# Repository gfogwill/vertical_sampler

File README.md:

# Vertical Sampler

Firmware, hardware and host software for a balloon-borne vertical air sampler for Ice Nucleating Particle (INP) collection.

Payload and ground-station Raspberry Pi Pico W boards run **CircuitPython** and
communicate over **LoRa at 868 MHz**. The system supports the airborne payloads
`alma` and `beni`, plus the ground-operated payload `carla`.

## System Overview

```text
┌─────────────────────────┐        LoRa 868 MHz         ┌─────────────────────────┐
│        PAYLOAD          │◄───────────────────────────►│    GROUND STATION       │
│  Raspberry Pi Pico W    │                             │  Raspberry Pi Pico W    │
│                         │                             │                         │
│  - GPS (+ RTC sync)     │                             │  - Receives telemetry   │
│  - SHT85 RH/temp sensor │                             │  - Relays to PC via USB │
│  - LPS25H pressure      │                             │  - Forwards commands    │
│  - Pumps + optional     │                             └─────────────────────────┘
│    electrovalve / OPC   │
│  - SD logging           │                                         │
│  - Battery + flow meter │                                    USB Serial
│  - Watchdog             │                                         │
└─────────────────────────┘                             ┌─────────────────────────┐
                                                        │       Host computer     │
                                                        │ host/cli.py             │
                                                        │ host/quickview.py       │
                                                        └─────────────────────────┘
```

## Repository Structure

```text
vertical_sampler/
├── firmware/                    # CircuitPython code deployed to Pico boards
│   ├── common/                  # Copied flat to every CIRCUITPY drive
│   │   ├── config.py            # PCB v1 GPIOs, calibration, limits, LoRa addresses
│   │   ├── payload.py           # Active payload drivers and mission loop
│   │   ├── lora.py              # RFM9x wrapper
│   │   ├── pressure_sensor.py   # LPS25H driver
│   │   ├── sdcard.py            # SD mount, JSONL data and log writes
│   │   ├── logging.py
│   │   ├── pack.py              # Binary LoRa telemetry format
│   │   ├── led.py
│   │   ├── adafruit_gps.py      # Vendored CircuitPython dependency
│   │   └── adafruit_rfm9x.py    # Vendored CircuitPython dependency
│   ├── alma_main.py             # Alma airborne payload entry point
│   ├── beni_main.py             # Beni airborne payload entry point
│   ├── carla_main.py            # Carla ground payload entry point
│   └── ground_main.py           # Ground-station entry point
├── host/                        # Python 3 programs running on the control PC
│   ├── cli.py
│   └── quickview.py
├── pcb/                         # KiCad PCB v1 project
├── docs/
│   └── TROUBLESHOOTING.md
├── Makefile
└── README.md
```

`firmware/common/` is copied as flat modules to the root of `CIRCUITPY`. CircuitPython imports therefore remain simple:

```python
import config
import lora
import pack
```

## Payload Identities

| Unit | LoRa node address | Hardware | Entry point |
|---|---:|---|---|
| Ground station | `0x47` | Serial/LoRa bridge | `firmware/ground_main.py` |
| Alma | `0x93` | Two pumps, electro-valve, OPC-N3 | `firmware/alma_main.py` |
| Beni | `0x71` | Two pumps, electro-valve, OPC-N3 | `firmware/beni_main.py` |
| Carla | `0x72` | Front pump only; no electro-valve or OPC-N3 | `firmware/carla_main.py` |

Addresses, GPIO assignments, calibration constants and safety limits are defined centrally in `firmware/common/config.py`.

## Quick Start

### 1. Flash CircuitPython

```bash
make download-circuitpython-image
```

Copy the resulting `.uf2` to the Pico W while it is in BOOTSEL mode.

### 2. Install dependencies

The repository vendors `adafruit_gps.py` and `adafruit_rfm9x.py`. Install the remaining required CircuitPython libraries in the Pico `lib/` directory, including the dependencies required by the RFM9x driver such as `adafruit_bus_device`.

### 3. Deploy firmware

Set the CircuitPython mount point if needed:

```bash
export CIRCUITPY_PATH=/media/$USER/CIRCUITPY
```

Deploy the required device image:

```bash
make update-alma
make update-beni
make update-carla
make update-ground
```

Each target:

1. Removes stale `code.py`.
2. Copies all `firmware/common/*.py` modules to the Pico.
3. Copies the selected entry point as `main.py`.

### 4. Control a payload

Run commands from the host computer:

```bash
python host/cli.py data alma
python host/cli.py pump alma front on
python host/cli.py pump beni back off
python host/cli.py valve beni on
python host/cli.py data carla
python host/cli.py pump carla front on
```

For bench testing, the Alma or Beni payload can also accept actuator commands
directly over its own USB connection. Deploy the updated payload firmware first,
then run the USB helper from the laptop:

```bash
python host/usb_payload.py --port /dev/ttyACM0 pump front on
python host/usb_payload.py --port /dev/ttyACM0 data
python host/usb_payload.py --port /dev/ttyACM0 pump front off
```

The `--port` option can be omitted when exactly one Pico serial device is
connected. The helper waits for a JSON acknowledgement and exits; the pump
state is not tied to the helper process or USB connection. Alma/Beni must
remain separately powered after the laptop is disconnected, and the normal
battery/temperature safety interlock still applies. The direct USB path
accepts `pump front|back|both on|off`, `valve on|off`, and `data`.

Scheduled commands can be sent from a text file using UTC ISO-8601
timestamps. The command after each timestamp uses the same syntax as the
one-shot CLI commands:

```text
# timestamp command payload [location] state
2026-09-26T12:00:00Z pump alma front on
2026-09-26T12:30:00Z valve beni off
2026-09-26T13:00:00+00:00 pump alma front off
```

An editable example is provided in
[`sampling_schedule.example.txt`](sampling_schedule.example.txt). Copy it
to a working schedule, then change and review the timestamps before running:

```bash
cp sampling_schedule.example.txt sampling_schedule.txt
python host/cli.py schedule sampling_schedule.txt --dry-run
```

Run the schedule with:

```bash
python host/cli.py schedule sampling_schedule.txt
```

To run the schedule together with the monitor and JSON telemetry logging,
use the monitor mode so both features share one serial connection:

```bash
python host/cli.py monitor \
  --schedule sampling_schedule.txt \
  --json-output telemetry.jsonl
```

`--json-output` is an alias for `--log-file`. Add
`--schedule-run-past-due` if entries from before startup should be executed
immediately.

Entries that are already past when the scheduler starts are skipped by
default. Use `--run-past-due` to execute them immediately, or
`--dry-run` to validate and print the schedule without sending commands.
For scheduled actuator commands, the host by default waits 5 seconds after
each send, requests fresh payload telemetry, and checks the requested pump or
valve state. If the state is not confirmed, the command is sent again, up to
three total attempts. A command that was applied but whose acknowledgement was
lost is not resent when the later state check confirms the requested state.

The standalone scheduler accepts `--verify-delay SECONDS` and
`--max-attempts COUNT`. Monitor schedules use the corresponding
`--schedule-verify-delay` and `--schedule-max-attempts` options. These options
apply only to pump and valve commands; `data` entries retain their existing
telemetry retry behavior.

`host/quickview.py` is available for local data inspection and visualization.
It displays separate Alma and Beni OPC-N3 heatmaps using the standard
0.35–40 µm diameter bins on a logarithmic diameter axis. Heatmap colors use
logarithmic normalization and are corrected to counts per logarithmic diameter
interval (`dN/dlog10(Dp)`). New telemetry includes the OPC histogram sample
period, so QuickView and the plotting scripts normalize distributions to
particles/cm³. Older logs without that field remain relative unless a known
period is passed explicitly, for example:

```bash
python host/quickview.py --log-file ground_dump.jsonl \
    --opc-sampling-period-s <seconds>
```
All shared time axes are explicitly formatted in UTC. QuickView prefers the
payload UTC/RTC timestamp, then the host log timestamp; when a payload has no
valid absolute clock, its `monotonic_s` intervals are retained instead of
assigning one artificial second per log line.
Carla is included in the common sensor plots but has no OPC or electro-valve
controls.

For daily low-cloud measurement planning at Matorova, install the weather
dashboard dependencies and launch:

```bash
python -m pip install -r host/requirements-weather.txt
python host/weather_dashboard.py
```

The dashboard refreshes every 10 minutes and combines:

- ECMWF IFS boundary-layer height, retrieved through Open-Meteo.
- Altitude-resolved cloud fraction from Cloudnet's preferred forecast model
  for Kenttärova (normally MEPS), with liquid, ice and precipitating
  hydrometeor contours.
- Near-real-time cloud-base and cloud-top observations from ACTRIS Cloudnet at
  Kenttärova, visualized as Cloudnet target classifications for liquid,
  drizzle/rain, ice, mixed-phase and melting particles.
- The latest Kenttärova HATPRO microwave-radiometer temperature and relative
  humidity profile, including potential temperature for visually identifying
  stable layers and likely boundary-layer tops.
- The latest available 00 or 12 UTC Sodankylä radiosonde profile from the
  University of Wyoming archive, including low-level horizontal wind-speed
  and wind-direction lines with meteorological wind barbs at 100 m intervals.
  Half barbs represent 2.5 m/s, full barbs 5 m/s, and flags 25 m/s.

Cloudnet NetCDF files are cached under
`~/.cache/vertical_sampler/weather`, and are downloaded again only when their
portal metadata indicates an update. The large HATPRO file is refreshed at
most once per hour, and cached files older than seven days are removed. The
plots focus on the lowest 2 km above ground. Use `--refresh-minutes 0` for a static view or
`--output matorova-weather.png` to generate a PNG without opening a window.

The host dashboards automatically use the latest sea-level pressure observation
from FMI station `Kittilä Matorova` (`fmisid=101985`) as QNH. The value is
refreshed every 10 minutes through the public
[FMI WFS API](https://opendata.fmi.fi/wfs). If FMI is unavailable, the last
fresh FMI value is retained and then the manual/default value of 1013.25 hPa
is used. Pass `--qnh VALUE` to select a different fallback, or
`--no-auto-qnh` to disable automatic updates. Logged monitor samples include
`_qnh_hpa`, `_qnh_source` and `_qnh_observation_time` so derived altitude
remains traceable.

## Telemetry Format

Each payload sample is logged as JSONL when an SD card is available and sent over LoRa as a packed binary packet defined in `firmware/common/pack.py`.

| Field | Type | Description |
|---|---|---|
| `msg_type` | str | `telemetry`, `cmd_ack` or `cmd_err` |
| `payload_id` | str | `alma`, `beni` or `carla` |
| `rtc_time` | str | RTC timestamp in ISO 8601 format |
| `gps_time` | uint32/null | GPS UTC Unix epoch |
| `gps_latitude` | float/null | Degrees |
| `gps_longitude` | float/null | Degrees |
| `gps_altitude` | float/null | Metres |
| `rh_sensor_humidity` | float | Relative humidity, % |
| `rh_sensor_temperature` | float | Temperature, °C |
| `pressure_sensor_pressure` | float | Pressure, mbar |
| `pressure_sensor_temperature` | float | Temperature, °C |
| `battery_voltage` | float | Calibrated 6S battery voltage |
| `cpu_temperature` | float | Pico internal temperature, °C |
| `sd_card_available` | int/null | 1 when the payload mounted the SD card successfully; 0 when mounting was unavailable; older packets report unavailable |
| `flow` | float | Standard L/min |
| `uplink_rssi` | int/null | Last ground-to-payload command RSSI measured by the payload, dBm |
| `downlink_rssi` | int/null | Current payload-to-ground packet RSSI measured by the ground station, dBm |
| `pump_front_state` | int | 0 or 1 |
| `pump_back_state` | int/null | 0 or 1; unavailable on Carla |
| `valve_state` | int/null | 0 or 1; unavailable on Carla |
| `opc_bin_0` ... `opc_bin_23` | uint16/null | Raw OPC-N3 particle counts per histogram bin |
| `opc_temperature` | float/null | OPC temperature, °C |
| `opc_humidity` | float/null | OPC relative humidity, %RH |
| `opc_sample_flow` | float/null | OPC sample flow, mL/s |
| `opc_sampling_period_s` | float/null | OPC histogram sampling period, s |
| `opc_laser_status` | int/null | OPC laser status |

For a histogram with a valid flow and sampling period, the instrument-reported
number concentration for each bin is:

```text
particles/cm³ = raw_bin_count / (opc_sample_flow * opc_sampling_period_s)
```

The conversion uses the measured per-histogram sample volume; it is a number
concentration reported by the OPC, not a mass concentration or a correction
for optical efficiency, coincidence losses, inlet losses, humidity, or particle
refractive index. Historical logs that predate `opc_sampling_period_s` can be
plotted with `--opc-sampling-period-s <seconds>` only when that period is known.

The current binary telemetry format is shared by all payloads. The ground
station also accepts the immediately preceding packet format and legacy
pre-OPC packets; those formats decode `opc_sampling_period_s` and
`sd_card_available` as unavailable. In `cli.py monitor`, the System section
shows this field as `YES` or `NO`.
Carla sends fill values for the unavailable back pump, electro-valve and OPC-N3
fields.
Commands targeting those unavailable devices are rejected by both the host
CLI and Carla firmware.

> **RTC synchronization:** on the first valid GPS fix, the payload sets the onboard RTC to GPS UTC. Subsequent `rtc_time` values remain valid even if the GPS temporarily loses its fix.

## SD Logging

The SD-card handler writes:

| File | Content |
|---|---|
| `/sd/<payload_id>_log.txt` | Human-readable events and diagnostics |
| `/sd/<payload_id>_NNN.jsonl` | One JSON object per sample cycle |

If the SD card is unavailable or fails while operating, the payload continues running and transmitting telemetry over LoRa. Logging degrades to the serial console instead of stopping the mission.

The `sd_card_available` telemetry field reports whether the card mounted
successfully and was available to the logger. It is not a hot-plug sensor:
removing or inserting a card after boot is not reported until the payload is
restarted and mounts the card again.

## Safety Features

| Condition | Threshold | Action |
|---|---:|---|
| Battery warning | ≤ 19.8 V | Warning logged |
| Battery critical | ≤ 18.6 V | Pumps off, valve off, error logged |
| CPU temperature warning | ≥ 45 °C | Warning logged |
| CPU temperature critical | ≥ 55 °C | Pumps off, valve off, error logged |
| Main-loop stall | 30 s watchdog timeout | Pico reset |

The watchdog is fed in the main loop, GPS wait loop, LoRa receive loop and failure-report loops.

## PCB v1 Pin Map

| Function | Pico GPIO |
|---|---:|
| GPS UART TX/RX | GP0 / GP1 |
| I2C SDA/SCL | GP2 / GP3 |
| Pump front | GP6 |
| Electrovalve | GP7 |
| SD chip select | GP9 |
| SPI SCK/MOSI/MISO | GP10 / GP11 / GP12 |
| LoRa chip select | GP16 |
| OPC chip select (reserved) | GP17 |
| Pump back | GP21 |
| Battery monitor ADC | GP27 |
| Flowmeter ADC | GP28 |

The RFM9x reset line is not routed on PCB v1. `config.LORA_RESET_DUMMY` remains because the CircuitPython RFM9x driver requires a reset-pin argument.

## Calibration

### Flowmeter

The TSI 4121 flowmeter is configured as:

- Signal range: 0–4 V corresponding to 0–20 Std L/min.
- ADC divider: 10 kΩ series resistor and 32.6 kΩ to ground.
- Divider ratio: \(32.6 / (10.0 + 32.6)\).
- Zero offset: `FLOW_OFFSET_LMIN` in `firmware/common/config.py`.

### Battery monitor

`BATTERY_CAL_FACTOR` in `firmware/common/config.py` converts the Pico ADC voltage to the measured 6S battery voltage. Recalibrate against a multimeter if the divider or analog front-end changes.

## Development Notes

- `firmware/common/payload.py` contains the active, hardware-validated payload drivers and mission loop.
- `firmware/common/config.py` is the single source of truth for PCB pins, calibration, operating limits and LoRa addresses.
- The old breadboard firmware is preserved in the `old_hardware` branch.
- See `docs/TROUBLESHOOTING.md` for deployment and communication diagnostics.

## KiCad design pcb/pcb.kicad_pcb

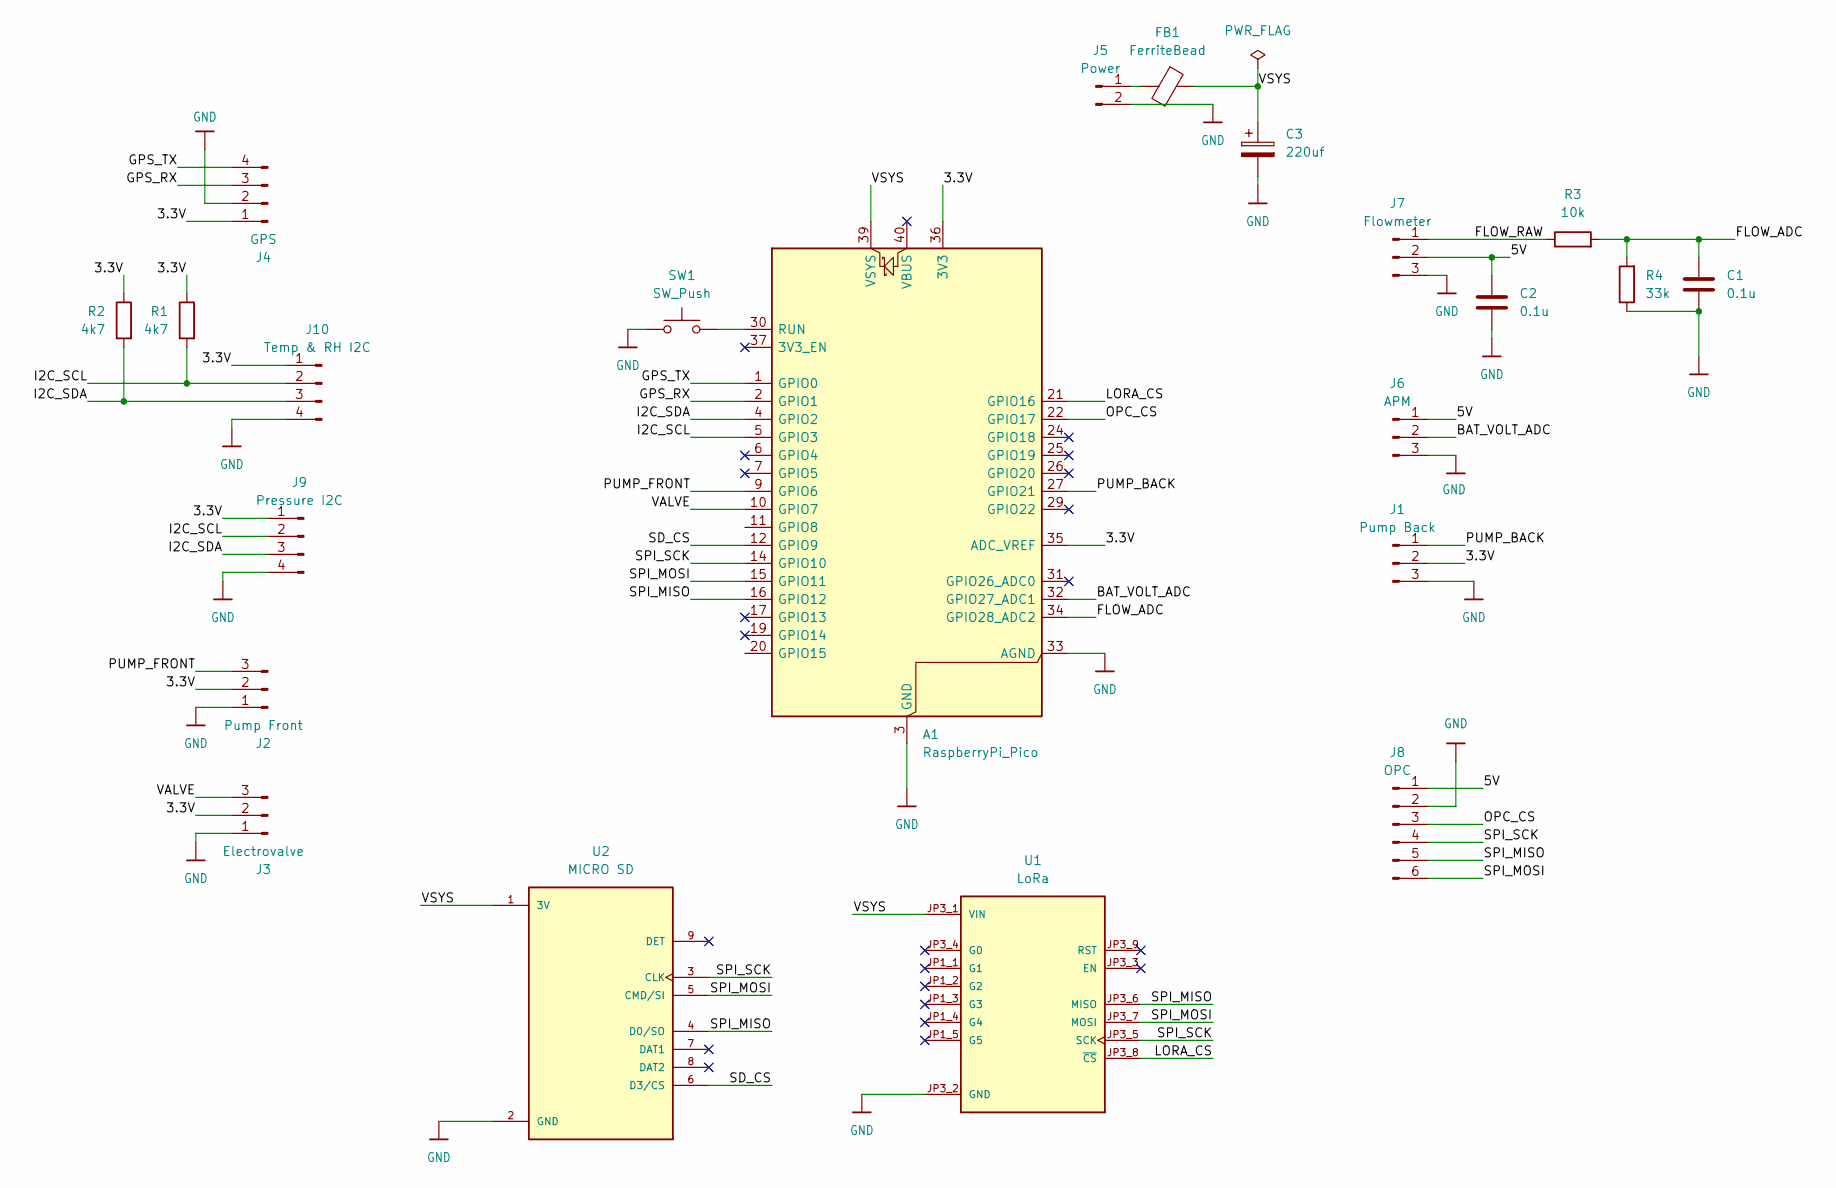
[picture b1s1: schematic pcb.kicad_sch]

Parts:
A1: RaspberryPi_Pico; RaspberryPi_Pico_Common_THT
C1, C2: 0.1u; C_1206_3216Metric
C3: 220uf; CP_Radial_D6.3mm_P2.50mm
FB1: FerriteBead; L_1206_3216Metric
J1: Pump Back; JST_XH_B3B-XH-A_1x03_P2.50mm_Vertical
J2: Pump Front; JST_XH_B3B-XH-A_1x03_P2.50mm_Vertical
J3: Electrovalve; JST_XH_B3B-XH-A_1x03_P2.50mm_Vertical
J4: GPS; JST_XH_B4B-XH-A_1x04_P2.50mm_Vertical
J5: Power; JST_XH_B2B-XH-A_1x02_P2.50mm_Vertical
J6: APM; JST_XH_B3B-XH-A_1x03_P2.50mm_Vertical
J7: Flowmeter; JST_XH_B3B-XH-A_1x03_P2.50mm_Vertical
J8: OPC; JST_XH_B6B-XH-A_1x06_P2.50mm_Vertical
J9: Pressure I2C; JST_XH_B4B-XH-A_1x04_P2.50mm_Vertical
J10: Temp & RH I2C; JST_XH_B4B-XH-A_1x04_P2.50mm_Vertical
R1, R2: 4k7; R_1206_3216Metric
R3: 10k; R_1206_3216Metric
R4: 33k; R_1206_3216Metric
SW1: SW_Push; SW_PUSH_6mm
U1: LoRa; MODULE_3073; PARTREV 2023-10-24
U2: MICRO SD; MODULE_MICROSD_SPI_OR_SDIO_CARD; PARTREV B

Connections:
/3.3V: A1.35 (ADC_VREF), A1.36 (3V3), J1.2, J2.2, J3.2, J4.1, J9.1, J10.1, R1.1, R2.1
/5V: C2.1, J6.1, J7.2, J8.1
/BAT_VOLT_ADC: A1.32 (GPIO27_ADC1), J6.2
/FLOW_ADC: A1.34 (GPIO28_ADC2), C1.1, R3.2, R4.2
/FLOW_RAW: J7.1, R3.1
/GPS_RX: A1.2 (GPIO1), J4.3
/GPS_TX: A1.1 (GPIO0), J4.4
/I2C_SCL: A1.5 (GPIO3), J9.2, J10.2, R1.2
/I2C_SDA: A1.4 (GPIO2), J9.3, J10.3, R2.2
/LORA_CS: A1.21 (GPIO16), U1.JP3_8 (~CS)
/OPC_CS: A1.22 (GPIO17), J8.3
/PUMP_BACK: A1.27 (GPIO21), J1.1
/PUMP_FRONT: A1.9 (GPIO6), J2.3
/SD_CS: A1.12 (GPIO9), U2.6 (D3/CS)
/SPI_MISO: A1.16 (GPIO12), J8.5, U1.JP3_6 (MISO), U2.4 (D0/SO)
/SPI_MOSI: A1.15 (GPIO11), J8.6, U1.JP3_7 (MOSI), U2.5 (CMD/SI)
/SPI_SCK: A1.14 (GPIO10), J8.4, U1.JP3_5 (SCK), U2.3 (CLK)
/VALVE: A1.10 (GPIO7), J3.3
/VSYS: A1.39 (VSYS), C3.1, FB1.2, U1.JP3_1 (VIN), U2.1 (3V)
GND: A1.3 (GND), A1.8 (GND), A1.13 (GND), A1.18 (GND), A1.23 (GND), A1.28 (GND), A1.33 (AGND), A1.38 (GND), C1.2, C2.2, C3.2, J1.3, J2.1, J3.1, J4.2, J5.2, J6.3, J7.3, J8.2, J9.4, J10.4, R4.1, SW1.1, U1.JP3_2 (GND), U2.2 (GND)
unnamed: A1.30 (RUN), SW1.2
unnamed: FB1.1, J5.1

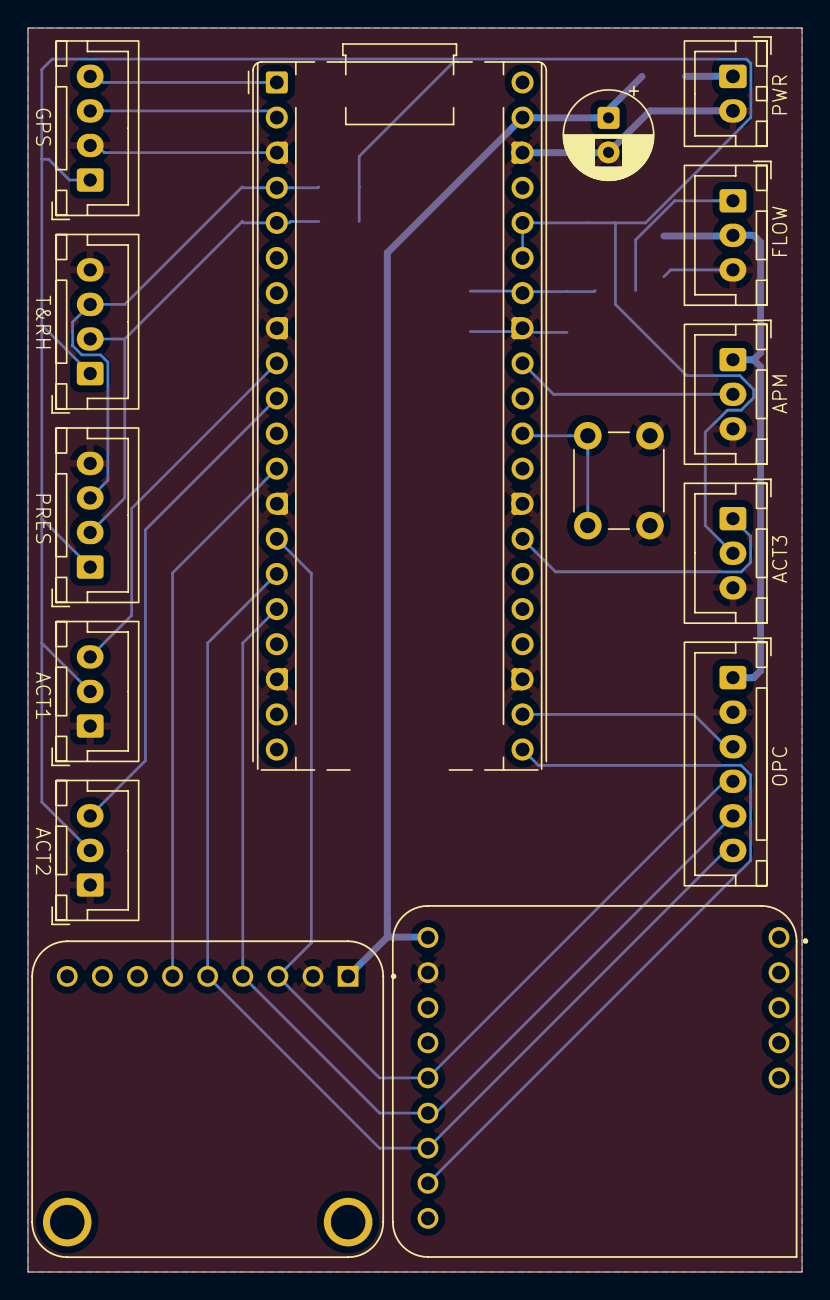
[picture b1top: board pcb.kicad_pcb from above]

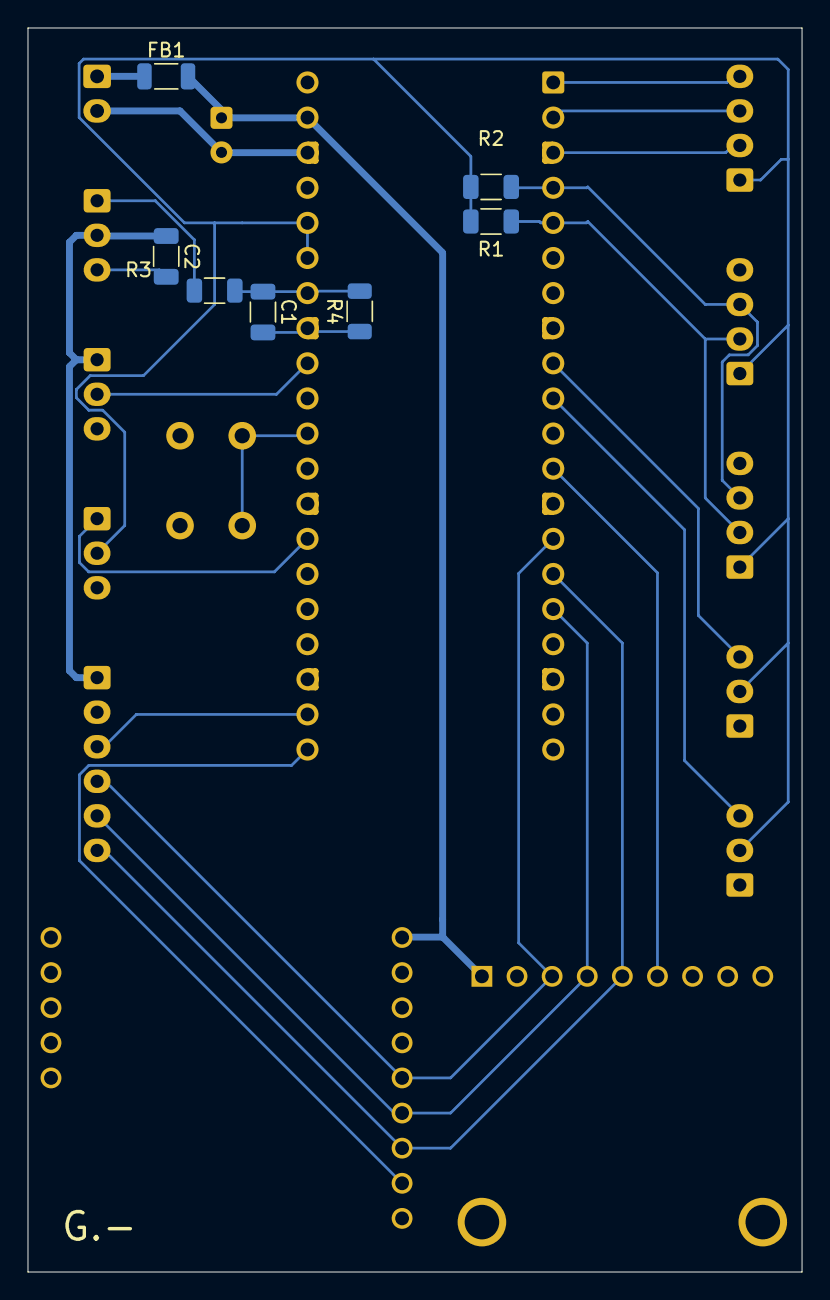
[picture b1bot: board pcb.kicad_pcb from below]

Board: 2 copper layers, 56.0 x 90.0 mm, 22 parts (7 on the bottom side), 22 nets.

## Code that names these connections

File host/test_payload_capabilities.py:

import importlib.util
import pathlib
import sys
import types
import unittest
from unittest.mock import patch
from types import SimpleNamespace
import json
import io
from contextlib import redirect_stdout


ROOT = pathlib.Path(__file__).resolve().parents[1]
if str(ROOT) not in sys.path:
    sys.path.insert(0, str(ROOT))
sys.modules.setdefault("serial", types.SimpleNamespace())

from host import cli


def load_pack_module():
    path = ROOT / "firmware" / "common" / "pack.py"
    spec = importlib.util.spec_from_file_location("payload_pack_test", path)
    module = importlib.util.module_from_spec(spec)
    spec.loader.exec_module(module)
    return module


def load_actuators_module():
    created = []

    class FakeOutput:
        def __init__(self, pin):
            self.pin = pin
            self.value = None
            created.append(self)

        def switch_to_output(self, value):
            self.value = value

    fake_digitalio = types.SimpleNamespace(DigitalInOut=FakeOutput)
    fake_config = types.SimpleNamespace(
        PUMP_FRONT="front-pin",
        PUMP_BACK="back-pin",
        ELECTROVALVE="valve-pin",
    )
    path = ROOT / "firmware" / "common" / "actuators.py"
    spec = importlib.util.spec_from_file_location("actuators_test", path)
    module = importlib.util.module_from_spec(spec)
    with patch.dict(
        sys.modules,
        {"digitalio": fake_digitalio, "config": fake_config},
    ):
        spec.loader.exec_module(module)
    return module, created


class PayloadCapabilityTests(unittest.TestCase):
    def test_campaign_payload_names(self):
        self.assertEqual(
            [str(payload) for payload in cli.Payload],
            ["alma", "beni", "carla"],
        )

    def test_data_command_does_not_require_actuator_state(self):
        with patch.object(sys, "argv", ["cli.py", "data", "carla"]):
            args = cli.parse_args()

        self.assertEqual(args.subcommand, "data")
        self.assertEqual(args.payload, cli.Payload.CARLA)

    def test_carla_accepts_front_pump(self):
        args = SimpleNamespace(
            payload=cli.Payload.CARLA,
            subcommand="pump",
            pump_location="front",
        )
        cli._validate_command_capability(args)

    def test_carla_rejects_unavailable_actuators(self):
        for subcommand, location in (("pump", "back"), ("pump", "both")):
            args = SimpleNamespace(
                payload=cli.Payload.CARLA,
                subcommand=subcommand,
                pump_location=location,
            )
            with self.assertRaises(ValueError):
                cli._validate_command_capability(args)

        args = SimpleNamespace(payload=cli.Payload.CARLA, subcommand="valve")
        with self.assertRaises(ValueError):
            cli._validate_command_capability(args)

    def test_alma_and_beni_keep_opc_and_valve_capabilities(self):
        for payload in (cli.Payload.ALMA, cli.Payload.BENI):
            capabilities = cli._PAYLOAD_CAPABILITIES[payload]
            self.assertIn("opc", capabilities)
            self.assertIn("valve", capabilities)
            self.assertIn("pump_back", capabilities)

    def test_carla_uses_fill_values_in_common_wire_format(self):
        pack = load_pack_module()
        packet = pack.dict2bytes({
            "payload_id": "carla",
            "pump_front_state": 0,
            "pump_back_state": None,
            "valve_state": None,
        })
        decoded = pack.bytes2dict(packet)

        self.assertEqual(decoded["payload_id"], "carla")
        self.assertEqual(decoded["pump_front_state"], 0)
        self.assertEqual(decoded["pump_back_state"], pack.INT_FILLVAL)
        self.assertEqual(decoded["valve_state"], pack.INT_FILLVAL)
        self.assertEqual(decoded["opc_bin_0"], pack.UNSIGNED_SHORT_FILLVAL)

    def test_radio_packet_carries_payload_measured_uplink_rssi(self):
        pack = load_pack_module()
        packet = pack.dict2bytes({
            "payload_id": "alma",
            "uplink_rssi": -87,
        })
        decoded = pack.bytes2dict(packet)

        self.assertEqual(decoded["uplink_rssi"], -87)
        self.assertNotIn("downlink_rssi", decoded)

    def test_old_rssi_field_is_treated_as_uplink(self):
        data = {"rssi": -91}

        cli._normalize_signal_fields(data)

        self.assertEqual(data["uplink_rssi"], -91)

    def test_non_finite_rssi_is_treated_as_unavailable(self):
        data = {
            "uplink_rssi": float("nan"),
            "downlink_rssi": float("inf"),
        }

        cli._normalize_signal_fields(data)

        self.assertIsNone(data["uplink_rssi"])
        self.assertIsNone(data["downlink_rssi"])
        self.assertEqual(cli._fmt_value("downlink_rssi", float("nan")), ("N/A", True))

    def test_system_values_are_printed_before_opc_values(self):
        data = {
            "battery_voltage": 23.4,
            "uplink_rssi": -90,
            "downlink_rssi": -82,
            "opc_temperature": 20.0,
        }
        output = io.StringIO()

        with redirect_stdout(output):
            cli.pretty_print(data, payload_id="alma")

        rendered = output.getvalue()
        self.assertLess(rendered.index("System"), rendered.index("OPC"))
        self.assertIn("RSSI ground->payload", rendered)
        self.assertIn("RSSI payload->ground", rendered)

    def test_front_only_pump_does_not_claim_back_output(self):
        actuators, created = load_actuators_module()
        logger = types.SimpleNamespace(info=lambda _message: None)
        pump = actuators.Pump(logger, locations=("front",))

        self.assertEqual(
            [output.pin for output in created],
            ["front-pin", "back-pin"],
        )
        self.assertEqual(pump.front_state(), 0)
        self.assertIsNone(pump.back_state())
        with self.assertRaises(ValueError):
            pump.set_state("back", "on")
        with self.assertRaises(ValueError):
            pump.set_state("both", "on")

    def test_ground_bridge_errors_are_returned_immediately(self):
        message = {
            "error": "command transmitted but no payload acknowledgement received",
            "stage": "payload_ack",
            "payload_id": "alma",
        }

        class FakeSerial:
            in_waiting = 1

            def readline(self):
                self.in_waiting = 0
                return (json.dumps(message) + "\n").encode()

        response = cli._read_cmd_response(
            FakeSerial(),
            timeout_s=0.1,
            expected_payload=cli.Payload.ALMA,
        )

        self.assertEqual(
            response["_error"],
            "payload_ack: command transmitted but no payload acknowledgement received",
        )


if __name__ == "__main__":
    unittest.main()

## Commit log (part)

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2026-04-28 Initial commit: payload firmware, ground station, docs and Makefile
2026-04-28 Reorganize: common/ shared code, payloads/kenttarova and payloads/matorova, update Makefile and README
2026-04-28 Remove old payload/ dir (moved to common/ and payloads/)
2026-04-28 Refactor: separate common code from per-payload main.py (kenttarova + matorova)
2026-06-09 docs: add "No space left on device" troubleshooting entry
2026-06-09 feat: pretty-print telemetry data as formatted table in cli.py
2026-06-09 feat: add retry logic for data/cmd requests to handle payload listen window
2026-06-09 fix: cli filters non-JSON lines; ground sends ACK prefix to avoid echo confusion
2026-06-09 fix: rewrite ground/main.py with synchronous request-response pattern (like original)
2026-06-09 fix: correct syntax error in ground/main.py (misplaced .encode() parentheses)
2026-06-09 feat: add ground/boot.py to enable usb_cdc data port; update Makefile
2026-06-09 revert: remove boot.py, breaks Thonny connection and CDC setup
2026-06-09 fix: remove boot.py line from update-ground target
2026-06-09 fix: rewrite ground/main.py using sys.stdin (original working approach)
2026-06-09 fix: disable REPL echo in ground/main.py to prevent self-commands
2026-06-09 fix: remove debug kwarg from GPS, fix pump/valve response format, improve command listening window
2026-06-09 fix: remove supervisor.runtime.repl_mode_enabled (not available in CP 8.2.6)
2026-06-09 fix: battery monitor GP27, read actual flowmeter value from GP28
2026-06-15 fix: update FlowMeter.flow() formula for 10k/33k voltage divider and 4121 scale
2026-06-15 fix: correct flowmeter divider to 32.6k and add zero-flow offset calibration
2026-06-15 refactor: remove accidental common/ dir, move flowmeter fix into payload/payload.py
2026-06-15 chore: delete accidental common/ directory (payload.py)
2026-06-15 chore: delete accidental common/ directory (address.py)
2026-06-15 chore: delete accidental common/ directory (led.py)
2026-06-15 chore: delete accidental common/ directory (logging.py)
2026-06-15 chore: delete accidental common/ directory (lora.py)
2026-06-15 chore: delete accidental common/ directory (pack.py)
2026-06-15 chore: delete accidental common/ directory (pressure_sensor.py)
2026-06-15 chore: delete accidental common/ directory (sdcard.py)
2026-06-15 fix: update-common now copies from payload/ instead of removed common/
2026-06-15 Update flow offset calibration value
2026-06-16 feat: separate log/data files, auto-increment data filename per flight
2026-06-16 fix: update payload.py and main.py files for new SDCard/logger API
2026-06-16 feat: add rtc_time to data JSON and sync RTC from GPS fix
2026-06-16 feat: add CPU temperature monitoring and battery low-voltage pump cutoff
2026-06-16 fix: calibrate battery voltage factor to 10.15 and remove debug print
2026-06-16 feat: watchdog timer and graceful SD failure handling
2026-06-16 docs: update README with current data format, SD logging, safety features and calibration
2026-06-17 payload: add automatic heartbeat every 60 s with per-unit offset
    - HEARTBEAT_INTERVAL_S = 60
    - HEARTBEAT_OFFSET_S per payload_id (matorova=0, kenttarova=30)
    to reduce LoRa collision probability
    - heartbeat is a normal data packet sent via lora.send() using the
    last collected data dict, so no new data structure is introduced
    - uses time.monotonic() for drift-free scheduling inside main_loop
2026-06-17 cli: add 'monitor' subcommand with curses TUI
    - New top-level subcommand: monitor
    Usage: python cli.py monitor [--payloads matorova kenttarova] [--qnh 1013.25]
    - Two-column TUI (one per payload) with curses, auto-refreshing every
    POLL_INTERVAL_S (default 5 s) by polling 'data' on each payload
    - Pressure altitude computed from QNH and measured pressure (ISA formula)
    - Events pane: last 8 log lines at bottom
2026-06-17 pack+cli: add cpu_temperature to binary pack; fix curses boundary ERR
    pack.py:
    - Add cpu_temperature (float 'f') as last field in KEYS/FORMAT
    - Binary format is now 15 fields; both payload and ground must be
    reflashed together (format is not backwards-compatible)
    cli.py:
    - Fix curses addnstr() ERR: clamp every write to cols-1 to avoid
2026-06-17 cli: fix monitor keyboard freeze — move serial poll to background thread
    Problem: _poll_payload() blocks up to 6 s waiting for a LoRa response.
    While it blocks, curses getch() never runs so q/r/1/2 are ignored.
    Fix:
    - PollWorker thread owns the serial port and a queue for results
    - Main curses loop only calls getch() and reads from the queue —
    never blocks on serial
2026-06-17 ground+cli: passive heartbeat listen; control keys in monitor; remove auto-poll
    ground/main.py:
    - Main loop now calls lora.receive(timeout=1) when no serial command
    is waiting, so heartbeats from payloads are forwarded to the host
    as JSON without needing an explicit 'data' poll
    - Command handling unchanged
    cli.py:
2026-06-18 pack+cli: add payload_id (10s) to binary pack so heartbeats are identifiable
    payload/pack.py:
    - Add ("payload_id", "10s") at end of KEYS
    - dict2bytes: encode string to fixed 10-byte field, zero-padded
    - bytes2dict: decode bytes field, strip null bytes and spaces
    cli.py:
    - PollWorker._try_parse_heartbeat: match heartbeat to payload via
2026-06-18 pack: fix bytes padding for CircuitPython (no bytes.ljust)
2026-06-18 pack: fix bytes.decode for CircuitPython (no errors kwarg)
